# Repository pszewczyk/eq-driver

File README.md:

# eq-driver
A driver for equatorial telescope mounts

Sterownik napędu montażu paralaktycznego teleskopu.
Kompatybilne z EQ3-2.

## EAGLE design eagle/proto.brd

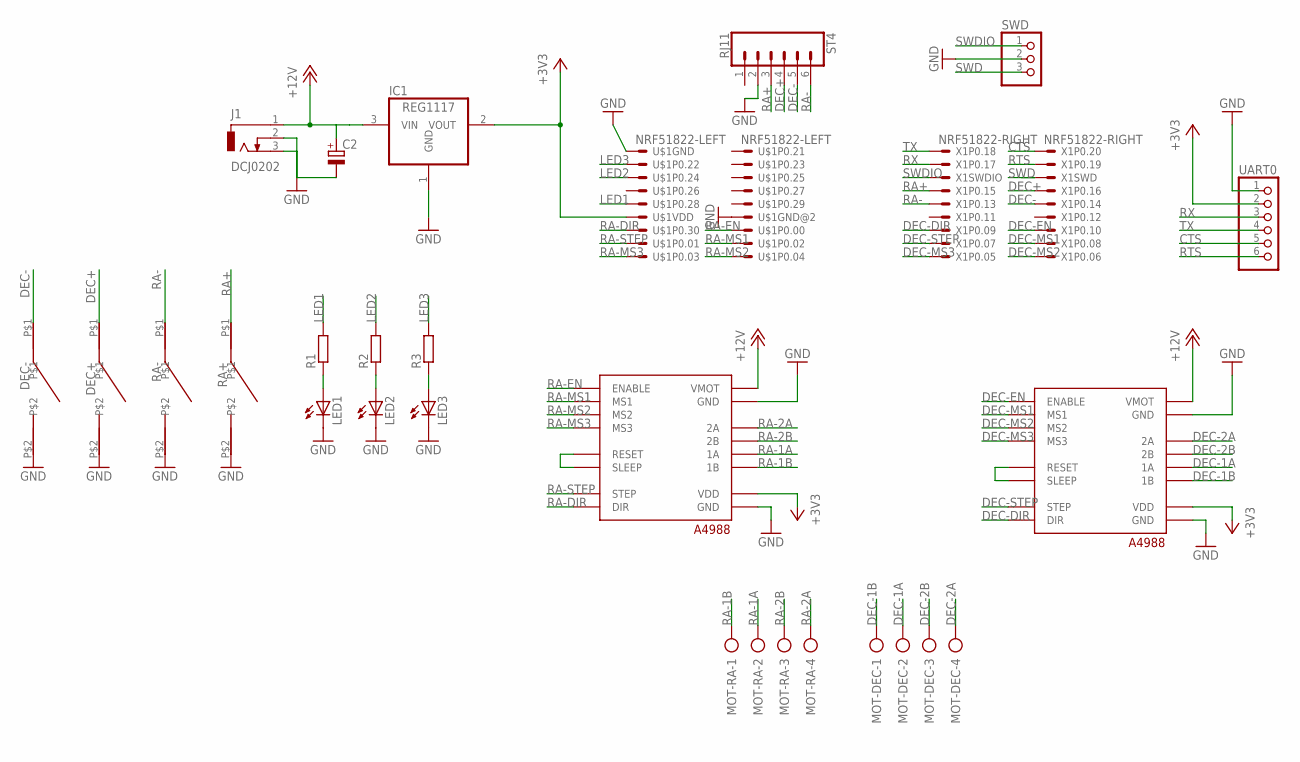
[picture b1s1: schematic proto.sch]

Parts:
C2: CPOL-EUSMCC; SMC_C
DEC+: TACT-SWITCH; TACT-SWITCH-THT
DEC-: TACT-SWITCH; TACT-SWITCH-THT
DRV-DEC: A4988_ALL
DRV-RA: A4988_ALL
IC1: REG1117; SOT223
J1: DCJ0202
LED1, LED2, LED3: LEDSML1206; SML1206
MOT-DEC: AK500/4
MOT-RA: AK500/4
R1, R2, R3: RR1206; R1206
RA+: TACT-SWITCH; TACT-SWITCH-THT
RA-: TACT-SWITCH; TACT-SWITCH-THT
ST4: RJ11; RJ11-6
SWD: PINHD-1X3; 1X03
U$1: NRF51822-LEFT
UART0: PINHD-1X6; 1X06
X1: NRF51822-RIGHT

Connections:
+3V3: DRV-DEC.P15 (VDD), DRV-RA.P15 (VDD), IC1.2 (VOUT), U$1.11, UART0.2
+12V: C2.+, DRV-DEC.P9 (VMOT), DRV-RA.P9 (VMOT), IC1.3 (VIN), J1.1
CTS: UART0.5, X1.2
DEC+: DEC+.P$1, ST4.4, X1.8
DEC-: DEC-.P$1, ST4.5, X1.10
DEC-1A: DRV-DEC.P13 (1A), MOT-DEC.2
DEC-1B: DRV-DEC.P14 (1B), MOT-DEC.1
DEC-2A: DRV-DEC.P11 (2A), MOT-DEC.4
DEC-2B: DRV-DEC.P12 (2B), MOT-DEC.3
DEC-DIR: DRV-DEC.P8 (DIR), X1.13
DEC-EN: DRV-DEC.P1 (ENABLE), X1.14
DEC-MS1: DRV-DEC.P2 (MS1), X1.16
DEC-MS2: DRV-DEC.P3 (MS2), X1.18
DEC-MS3: DRV-DEC.P4 (MS3), X1.17
DEC-STEP: DRV-DEC.P7 (STEP), X1.15
GND: C2.-, DEC+.P$2, DEC-.P$2, DRV-DEC.P10 (GND), DRV-DEC.P16 (GND), DRV-RA.P10 (GND), DRV-RA.P16 (GND), IC1.1 (GND), J1.2, J1.3, LED1.C, LED2.C, LED3.C, RA+.P$2, RA-.P$2, ST4.2, SWD.2, U$1.1, U$1.12, UART0.1
LED1: R1.2, U$1.9
LED2: R2.2, U$1.5
LED3: R3.2, U$1.3
unnamed: LED1.A, R1.1
unnamed: LED2.A, R2.1
unnamed: LED3.A, R3.1
unnamed: DRV-RA.P5 (RESET), DRV-RA.P6 (SLEEP)
unnamed: DRV-DEC.P5 (RESET), DRV-DEC.P6 (SLEEP)
RA+: RA+.P$1, ST4.3, X1.7
RA-: RA-.P$1, ST4.6, X1.9
RA-1A: DRV-RA.P13 (1A), MOT-RA.2
RA-1B: DRV-RA.P14 (1B), MOT-RA.1
RA-2A: DRV-RA.P11 (2A), MOT-RA.4
RA-2B: DRV-RA.P12 (2B), MOT-RA.3
RA-DIR: DRV-RA.P8 (DIR), U$1.13
RA-EN: DRV-RA.P1 (ENABLE), U$1.14
RA-MS1: DRV-RA.P2 (MS1), U$1.16
RA-MS2: DRV-RA.P3 (MS2), U$1.18
RA-MS3: DRV-RA.P4 (MS3), U$1.17
RA-STEP: DRV-RA.P7 (STEP), U$1.15
RTS: UART0.6, X1.4
RX: UART0.3, X1.3
SWD: SWD.3, X1.6
SWDIO: SWD.1, X1.5
TX: UART0.4, X1.1

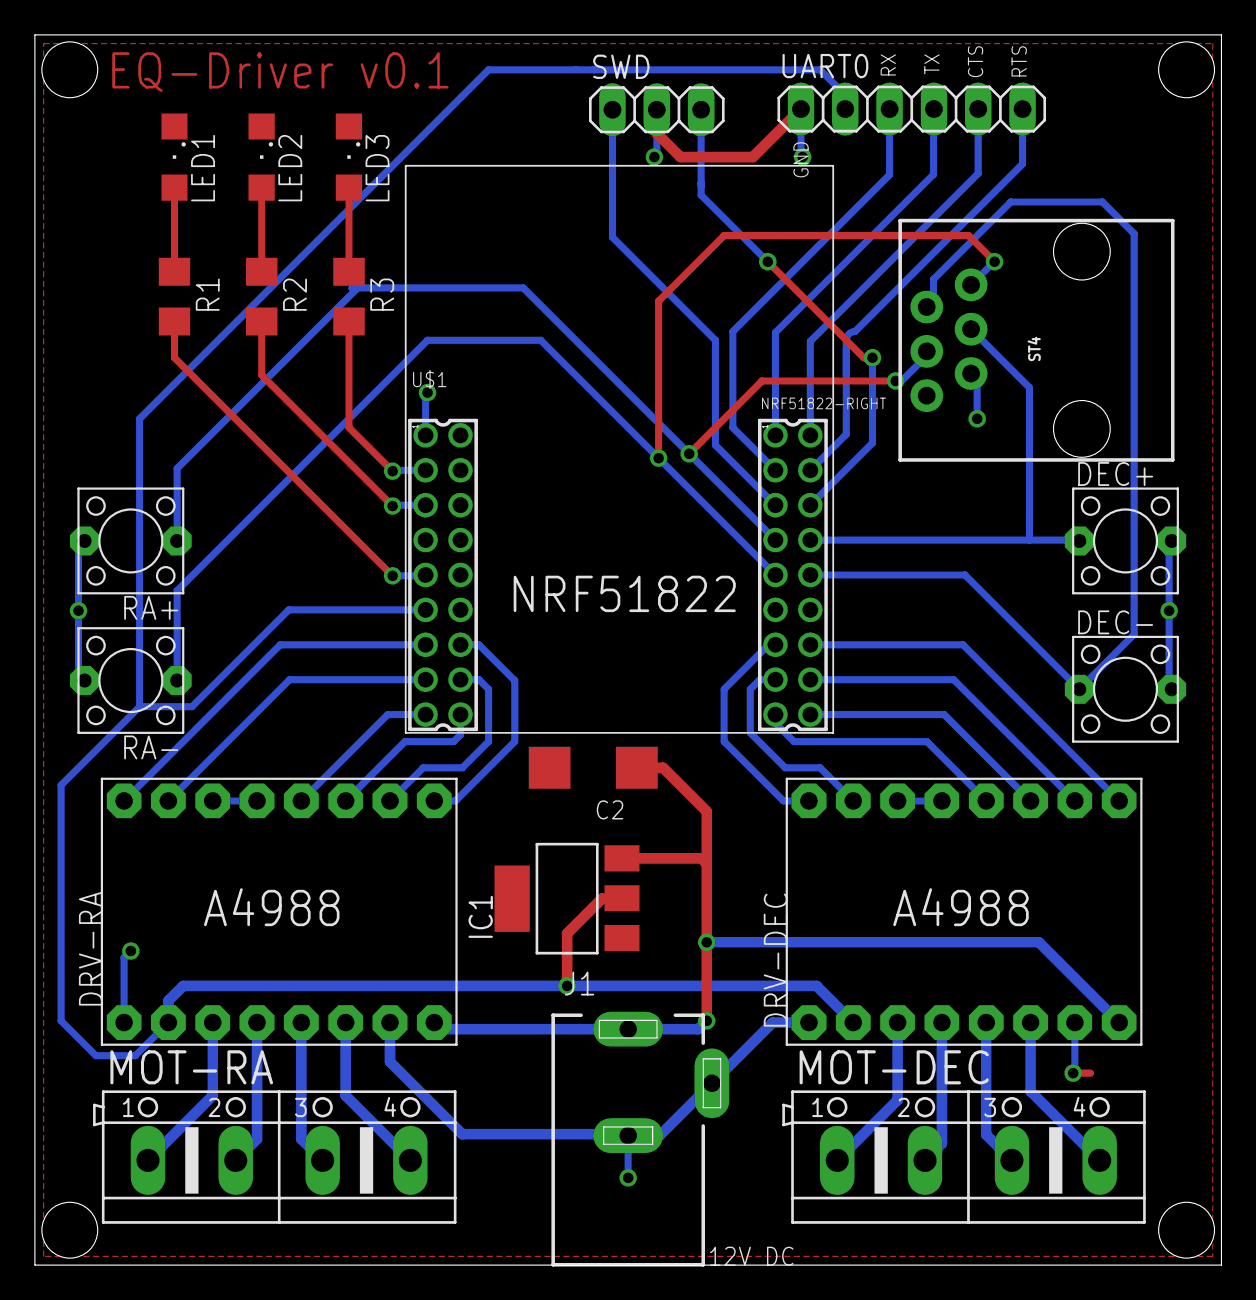
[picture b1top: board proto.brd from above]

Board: 2 copper layers, 68.0 x 70.5 mm, 22 parts (0 on the bottom side), 41 nets.

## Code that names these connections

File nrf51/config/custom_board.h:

/* This is custom board definition */

/* BLE400 board has some useful features like keys and leds */

#define KEY1 16
#define KEY2 17

#define KEY_RAP 16
#define KEY_RAM 17
#define KEY_DECP 14
#define KEY_DECM 15
 
#define LED0 18
#define LED1 19
#define LED2 20
#define LED3 21
#define LED4 22

#define CPCTS 8
#define CPRTS 10
#define CPRX 9
#define CPTX 11

#define RA_EN 0
#define RA_DIR 30
#define RA_STEP 1
#define RA_MS1 2
#define RA_MS2 4
#define RA_MS3 3

#define DEC_EN 10
#define DEC_DIR 9
#define DEC_STEP 7
#define DEC_MS1 8
#define DEC_MS2 6
#define DEC_MS3 5

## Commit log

2016-12-20 Some fixes
2017-01-23 Move Curie module to separate directory
    Making space for other modules/platforms
2017-01-23 Add nrf51 project skeleton
    Contains minimal building configuration. Still need nrf SDK to work.
2017-01-24 Simplify usage
2017-01-24 Add basics of BLE stack initialization
    Need additional sdk sources for compilation
2017-01-24 Enable required modules and add their sources
    Actually add all sources, ifdefs take care of unsed ones.
2017-01-24 Add GAP initialization
2017-01-24 Add advertising initialization & refactor
    No need to initialize on heap, while we can define everything as static structs.
2017-01-24 Add connection initialization
2017-01-24 Change error handling
2017-01-24 Add custom_board file for compatibilty
2017-01-24 Add bsp support
2017-01-26 Fix adresses in linker script
2017-01-26 Enable the clock module
    Enabling clock was a good idea. It works better enabled.
2017-03-23 Change makefile to makefile template
    Makefile is still prefered way of doing things in nrf environment. One could do autotools
    configuration or cmake, but for now simple template file with a few things to configure should do.
    Consider scripting it however.
2017-03-23 Add BLE400 pinout definition
    BLE400 have some useful features, probably the pinout will be copied in final board design.
2017-03-25 Add 'flah' makefile target
    Performs flashing using openocd. Openocd config file should be specified first.
2017-03-26 Add a timer
    Add correct implementation of a timer, not so obvious actually.
2017-03-26 Add service initialization
    Implements one service with one characteristic.
2017-03-29 Enable loggin debug messages over UART
2017-03-29 WIP Generalize service defining
    This commit introduces internal API for handling service initialization.
2017-03-30 Code refactorization
    Initial files separation, internal interfaces definitions
2017-04-04 Add board prototype
    It's one-sided board to cut the cost. Without some functionalities.
    Includes some lbr files for nrf51822 and a4988
2017-04-05 Add motor-related timers
2017-04-05 Add manual mode
    In manual mode user controls which way to go.
    TODO: Enable speed adjusting
2017-04-08 Enable updating ble characteristics
2017-04-08 Enable writing charatecteristics by external devices
2017-04-08 Clean up the code
2017-04-08 Add README file
2017-04-08 Cleanup and fixes
2017-04-09 WIP: Add android App
    This is just PoC of android client for the driver.
2017-04-11 Fix minor issues
2017-05-01 Add button handling and improve error handling
2017-05-01 goto: Fix spherical out of bounds problems
2017-05-09 eagle: Kolejna wersja prototypu
2017-05-09 nrf51: Eksport parametrów BLE do nagłówka
2017-05-16 Android: Add BLE service
2017-05-23 board: Change some elements to smd
2017-05-23 android: Add communication functionality
2017-05-25 Change more elements to smd
2017-05-25 Dodane tagi latexowe. Gotowe do uzycia jako \input.
2017-05-25 Dodano rozdzial o komunikacji
    Bluetooth
2017-05-25 Wstep.txt
2017-05-25 Dodano plik main.tex
2017-05-25 Architektura
2017-05-25 Dodano literaturę i opis sprzętu
2017-06-04 Dokumentacja projektu
2017-06-04 Add guiding support
2017-06-06 Fix disabled DEC motor in tracking mode
2017-06-06 eagle: Add ST4 port
2017-06-06 text: Add st4 documentation

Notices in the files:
parts and their libraries:
SparkFun-Connectors: Licensing: Creative Commons ShareAlike 4.0 International - https://creativecommons.org/licenses/by-sa/4.0
